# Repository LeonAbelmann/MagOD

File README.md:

# MagOD
Magnetic Optical Density meter
Tijmen Hageman, Jordi Hendrix, Hans Keizer, Marcel Welleweerd, Dave
van As, Ruthvik Bandaru, Rob Krawinkel, Leon Abelmann.

KIST Europe, University of Twente

## Other sources
Next to software, also the source codes to create hardware are
available here, as well as :

- Measurement head design, 3D print file (OpenSCAD, on [Thingiverse](https://www.thingiverse.com/thing:3122930) )
- Spice simulations, electronic diagrams, PCB layout (Spice, KiCad on
  [Dropbox](https://www.dropbox.com/sh/1dcai82byvd3hy0/AAA3AGXw0jbr9n2gzdcszufia))
- Laser cut pattern for housing electronics (DXF, on [Dropbox](https://www.dropbox.com/sh/1dcai82byvd3hy0/AAA3AGXw0jbr9n2gzdcszufia))

## Specifications
- Up to 800 samples per second, allows precise analysis of the rotation speed of magnetic bacteria
- Three-dimensional quasi-Helmholtz configuration, with fields up to 5 mT 
- Three color LED: red: 645 nm, 1000 mcd, green: 520 nm, 1700 mcd and blue 460 nm, 500 mcd
- Power supply with current feedback to compensate for coil heating, cut-off frequency 200 Hz
- Large area photodiode (sensitivity 0.5 mlx, with green LED theoretical max OD range of 5.8)
- Integrated pre-amplifier, SNR 83 dB (max OD range 4.0).
- Dedicated 16-bit ADS1115 DA converter
- Integrated temperature sensor
- Reference light detector
- Scattered light detector
- Fully programmable (ESP32 using Arduino IDE), open source
- User friendly spreadsheet recipe definition (csv format), with software to validate correctness
- Data collection on SD card, accessible by ftp over Wifi

## Additional info
- Marcel Welleweerd *and colleagues* (2022) ["An open-source automated magnetic optical density meter for analysis of suspensions of magnetic cells and particles"](https://doi.org/10.1063/5.0098008) Review of Scientific Instruments Vol 93, Issue 9, 094101. The manuscript can be found on [ArXiv](https://arxiv.org/abs/2106.07466)
- Chapter 8 in [Thesis](https://research.utwente.nl/en/publications/observing-magnetic-objects-in-fluids) Tijmen Hageman.
- [Presentation](https://youtu.be/TwwIsPg0qnI) by Leon Abelmann at Intermag2021

## How to join
Send mail to Leon (l.abelmann@tudelft.nl) if you are interested, all skills are welcome.

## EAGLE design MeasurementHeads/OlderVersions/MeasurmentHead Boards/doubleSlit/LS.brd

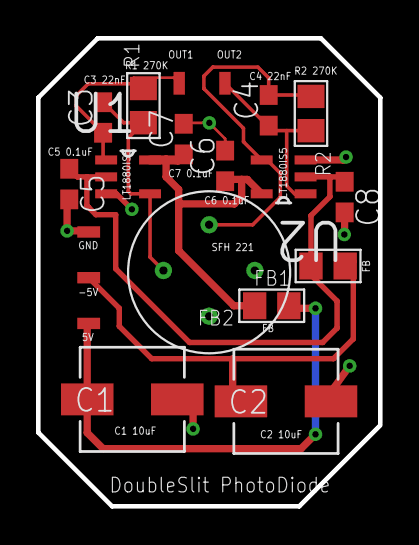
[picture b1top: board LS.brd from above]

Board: 2 copper layers, 19.0 x 26.0 mm, 17 parts (0 on the bottom side), 9 nets.

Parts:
C1, C2: EEEFC1V100R; CAP_EEFC_C
C3, C4: 22nF; C0603
C5, C6, C7, C8: 0.1uF; C0603
FB1, FB2: MMZ2012Y152B; 0805
J2: 22-28-8020
R1, R2: 270k; 0805
U1, U2: LT1880IS5TRMPBF; SOT95P280X100-5N
U$1: SFH221; SFH_221
U$2: PINHD_SMD-3

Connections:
5V: C1.1, FB2.1, U$2.1
-5V: C2.1, FB1.1, U$2.2
GND_ANALOG: C1.2, C2.2, C5.2, C6.2, C7.2, C8.2, U1.3, U2.3, U$1.CATHODE, U$1.METAL_CASE, U$2.3
unnamed: C4.1, J2.2, R2.2, U2.1
unnamed: C4.2, R2.1, U2.4, U$1.ANODE_B
unnamed: C3.1, J2.1, R1.2, U1.1
unnamed: C3.2, R1.1, U1.4, U$1.ANODE_A
V+(5V): C6.1, C7.1, FB2.2, U1.5, U2.5
V-(-5V): C5.1, C8.1, FB1.2, U1.2, U2.2

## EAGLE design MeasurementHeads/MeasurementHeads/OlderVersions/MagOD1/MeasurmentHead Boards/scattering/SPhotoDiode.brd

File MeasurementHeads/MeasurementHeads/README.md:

# Measurement head electronics
photoDiode : photodetector
refPhotoDiode: board to holde RBG led/LED-mono module and reference photodiode
RGBLed: RGB Led module
LED_mono: Monochrome led module

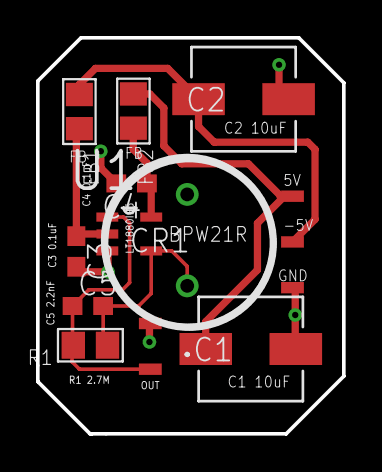
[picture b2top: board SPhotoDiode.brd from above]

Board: 2 copper layers, 17.0 x 22.0 mm, 12 parts (0 on the bottom side), 7 nets.

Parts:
C1, C2: EEEFC1V100R; CAP_EEFC_C
C3, C4: 0.1uF; C0603
C5: 2.2nF; C0603
CR1: BPW21R; TO99_BPW20RF
FB1, FB2: MMZ2012Y152B; 0805
J2: 22-28-8020
R1: 2.7M; 0805
U1: LT1880IS5TRMPBF; SOT95P280X100-5N
U$2: PINHD_SMD-3

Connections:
5V: C1.1, FB2.1, U$2.1
-5V: C2.1, FB1.1, U$2.2
GND_ANALOG: C1.2, C2.2, C3.2, C4.2, CR1.2, J2.2, U1.3, U$2.3
unnamed: C5.1, J2.1, R1.2, U1.1
unnamed: C5.2, CR1.1, R1.1, U1.4
V+(5V): C4.1, FB2.2, U1.5
V-(-5V): C3.1, FB1.2, U1.2

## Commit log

2019-01-13 Version that compiles and runs on Arduino Mega 2560 with 1.8" screen. Not tested on real MagOD
2019-01-13 moved globals to MagOD.h
2019-01-14 removed Testfunctions from repository
2019-01-23 tested on hardware, corrected errors in array intialization. Correct wrong threshold in button_left. Cosmetics here and there.
2019-04-07 added testfiles
2019-04-07 removed directory that should not be here
2019-04-07 removed directories from repository that were not fit for publishing yet
2019-04-07 added .gitignore to repo
2019-04-07 added README.md
2019-04-07 removed directories that are not ready to publish yet
2019-04-07 deleted arduino dir
2019-04-07 new files, confused now...
2019-04-07 changed README.md files
2019-04-07 removed TestTFT50 directory ,contains material that should not be publishe
2019-05-09 MagOD1 compiling and running Added Matlab code for analysis of datafiles
2019-07-06 Version for MagOD2 improved
2019-07-06 updated for MagOD hardware
2019-07-06 removed unnecessary pins.h
2019-08-26 new testfunctions
2019-08-26 update after testing new MagOD2
2019-09-18 made testarea for new recipes function
2019-09-18 redefined defintions, didn't work. added example
2019-09-19 added file read example
2019-09-21 changed file format
2019-09-26 made new examples
2019-10-17 Defined the array of recipes
2020-01-28 updated files
2020-02-15 Adjustable LED intensity during program. Test function for LED Test function for TFT screen
2020-03-18 Introduced ReadRecipes: read RECIPES.CSV from Flash card. First only test to check if recipe is read well.
2020-03-21 Try to test recipes reading on computer, rather than ESP32
2020-04-01 C++ file for testing the Recipes
2020-04-03 TestRecipes, split of the command line and Arduino versions in an organised way
2020-04-03 added TestRecipes.cpp (link)
2020-04-03 new recipes.csv
2020-04-04 fixed error with (char *)
2020-04-06 fixed makefile
2020-04-08 initialized file variable and file functions
2020-04-08 removed unnecessary files
2020-04-14 update with interupt based readout
2020-04-14 libray for interupt based readout
2020-04-17 SD card test
2020-05-20 new SD HTTP server test script
2020-05-27 Select samplerate ADC Recipes are read from csv file, recipes.* compatible with command line version
2020-05-27 Adapted MagOD.* for new recipes routines New testing routines
2020-05-27 removed binaries
2020-05-27 removed ReadSerial
2020-05-27 added directories to ignore
2020-05-27 removed testfunction
2020-05-27 removed testfunctions that should not be on repository
2020-05-30 moved password to separate (hidden) file. Adapted SD card access.
2020-05-31 Added display and selection of recipes. Adapted recipes.cpp of Ruthvik to MagOD environment. Fixed bug with first recipe step being skipped.
2020-05-31 Tweaks on screen layout. Added example RECIPES.CSV
2020-06-07 Corrected error in field calibration. Tweaked screen layout.
2020-07-10 Nasty bug in z-field, lost attachment to channel
2020-07-10 removed negative value correction
    from line 163 to 171
2020-08-14 fixed indentation to improve readability
2020-08-14 Added a new test implementing a queue after ADC0
2020-08-17 still some open files. not sure if commit is a good idea :(
2020-08-20 Added more comments to clarify the working of the queue test
2020-10-15 Modifications preparing for the Bayreuth system. Introduced calibration.h for all system dependent settings. Fixed error with Vref setting. Also switched on the led immediately after loading recipe.
2020-12-28 implemented ADC buffer, two cores, Wifi and ftp server
2021-01-03 Added NTP (time/date) support for timestamps of files on SD card, and file info for FTP client
2021-01-06 improved filename represenation
2021-01-06 improved README
2021-01-06 improved links in README
2021-01-06 fixed typo
2021-01-09 fixed Nr_cycles bug
2021-01-10 worked on graph, moved to new macbook
2021-01-17 autoscale graph and time info
2021-01-28 Max sequence error corrected, copy previous measurement in brown, changed some non necessary unsigned int to simple int
2021-02-14 fixed error for number of recipes sequences > 15. Experiments with python reading of data files
2021-02-14 corrected for missing parameters CEA/Bayreuth
2021-06-11 added license
2021-06-21 confusing
2021-09-01 fixed error in calculation OD on screen
2021-09-28 Implement autoCmag recipe, which calculates OD and Cmag automatically and displays on the touchscreen
2021-10-14 corrected version number
2021-10-24 Added screen reset. Code cleanup.
2022-07-05 Copied from Dropbox
2022-07-05 indicated files now also on github
2022-07-05 correct incorrect directory structure
